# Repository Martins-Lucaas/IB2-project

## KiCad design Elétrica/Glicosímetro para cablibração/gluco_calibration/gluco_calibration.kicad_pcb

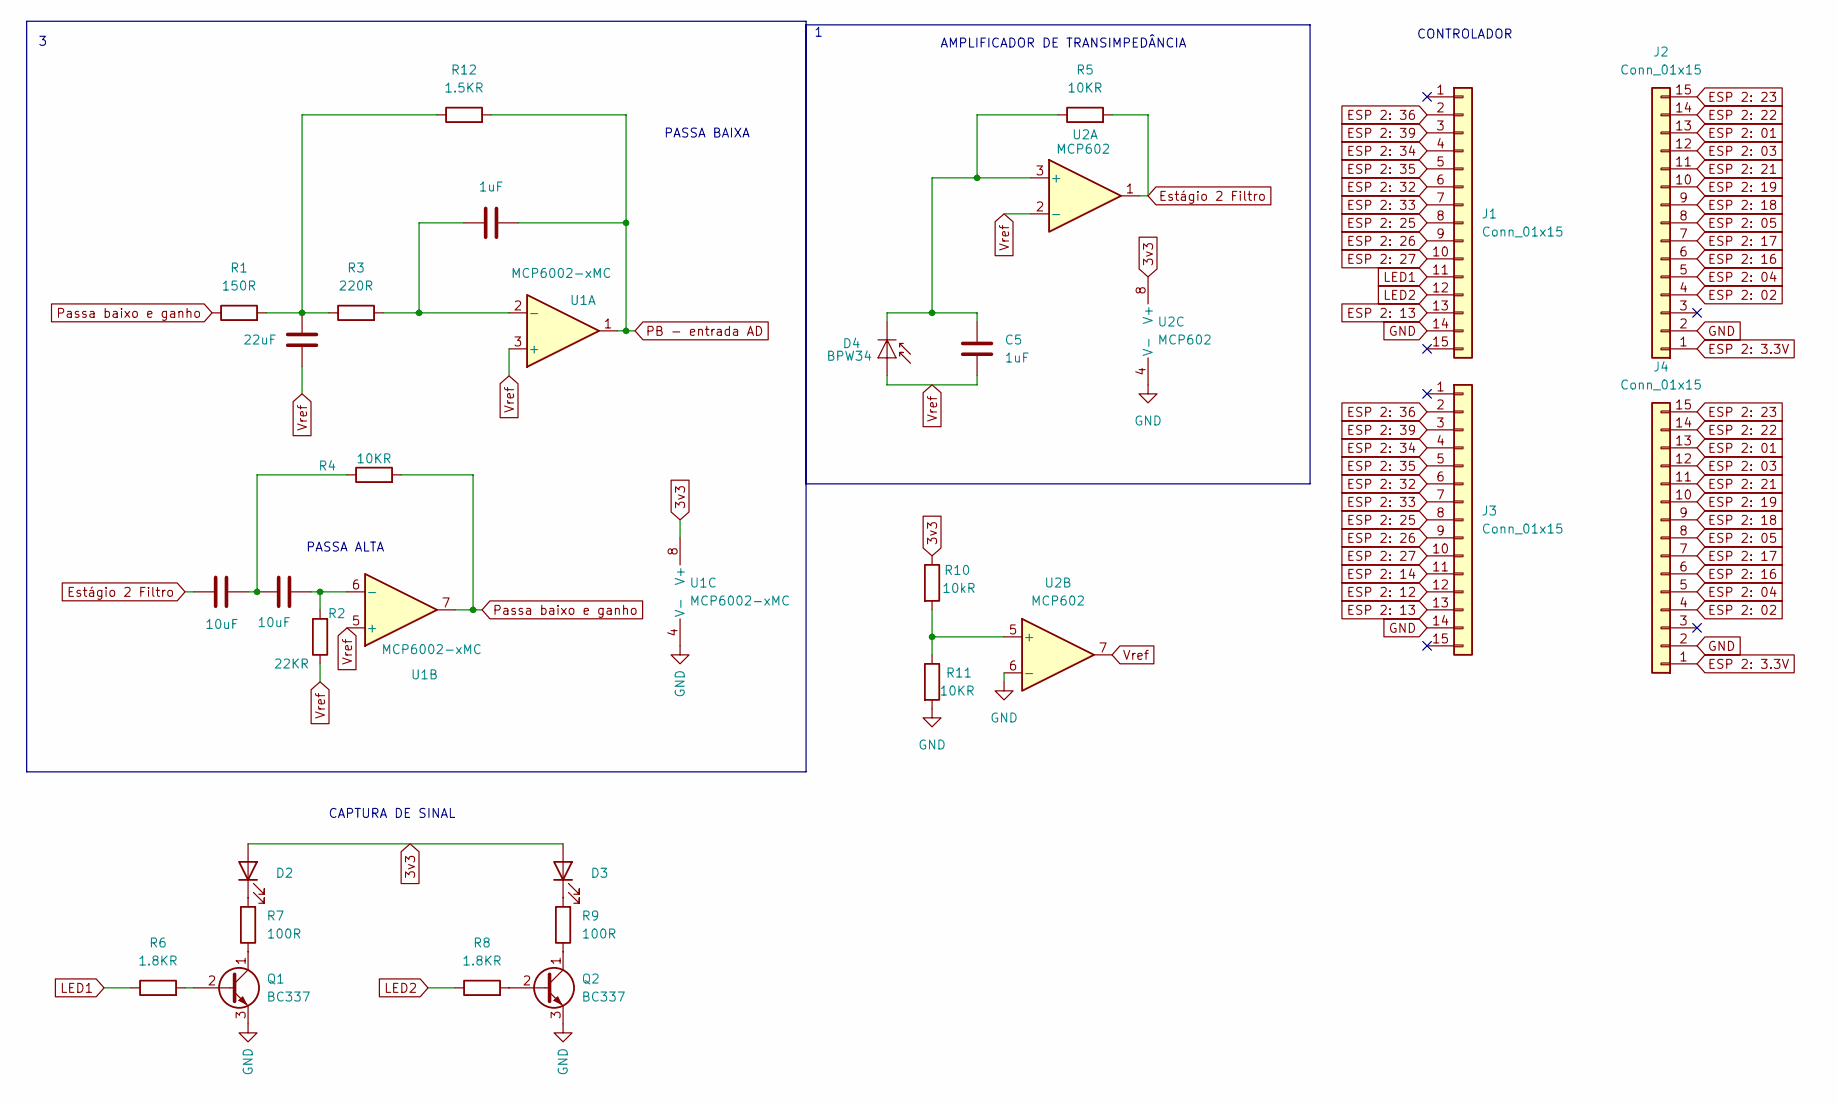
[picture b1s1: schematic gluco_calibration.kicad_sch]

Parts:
C1, C2: 10uF; C_Disc_D8.0mm_W2.5mm_P5.00mm
C3: 22uF; C_Disc_D8.0mm_W2.5mm_P5.00mm
C4, C5: 1uF; C_Disc_D8.0mm_W2.5mm_P5.00mm
D2: MTE8120CP 805nm; LED_D3.0mm_IRGrey
D3: MTE8120CP 805nm; LED_D3.0mm_Clear
D4: BPW34; Osram_DIL2_4.3x4.65mm_P5.08mm
J1, J2, J3, J4: Conn_01x15; PinSocket_1x15_P2.54mm_Vertical
Q1, Q2: BC337; TO-92_Inline
R1: 150R; R_Axial_DIN0204_L3.6mm_D1.6mm_P5.08mm_Horizontal
R2: 22KR; R_Axial_DIN0204_L3.6mm_D1.6mm_P5.08mm_Horizontal
R3: 220R; R_Axial_DIN0204_L3.6mm_D1.6mm_P5.08mm_Horizontal
R4, R5, R11: 10KR; R_Axial_DIN0204_L3.6mm_D1.6mm_P5.08mm_Horizontal
R6, R8: 1.8KR; R_Axial_DIN0204_L3.6mm_D1.6mm_P5.08mm_Horizontal
R7, R9: 100R; R_Axial_DIN0204_L3.6mm_D1.6mm_P5.08mm_Horizontal
R10: 10kR; R_Axial_DIN0204_L3.6mm_D1.6mm_P5.08mm_Horizontal
R12: 1.5KR; R_Axial_DIN0204_L3.6mm_D1.6mm_P5.08mm_Horizontal
U1: MCP6002-xMC; DFN-8-1EP_3x2mm_P0.5mm_EP1.75x1.45mm
U2: MCP602; DFN-8-1EP_3x2mm_P0.5mm_EP1.75x1.45mm

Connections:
3v3: D2.2 (A), D3.2 (A), R10.1, U1.8 (V+), U2.8 (V+)
ESP 2: 01: J2.13, J4.13
ESP 2: 02: J2.4, J4.4
ESP 2: 03: J2.12, J4.12
ESP 2: 3.3V: J2.1, J4.1
ESP 2: 04: J2.5, J4.5
ESP 2: 05: J2.8, J4.8
ESP 2: 12: J3.12
ESP 2: 13: J1.13, J3.13
ESP 2: 14: J3.11
ESP 2: 16: J2.6, J4.6
ESP 2: 17: J2.7, J4.7
ESP 2: 18: J2.9, J4.9
ESP 2: 19: J2.10, J4.10
ESP 2: 21: J2.11, J4.11
ESP 2: 22: J2.14, J4.14
ESP 2: 23: J2.15, J4.15
ESP 2: 25: J1.8, J3.8
ESP 2: 26: J1.9, J3.9
ESP 2: 27: J1.10, J3.10
ESP 2: 32: J1.6, J3.6
ESP 2: 33: J1.7, J3.7
ESP 2: 34: J1.4, J3.4
ESP 2: 35: J1.5, J3.5
ESP 2: 36: J1.2, J3.2
ESP 2: 39: J1.3, J3.3
Estágio 2 Filtro: C1.1, R5.2, U2.1
GND: J1.14, J2.2, J3.14, J4.2, Q1.3 (E), Q2.3 (E), R11.2, U1.4 (V-), U1.9 (V-), U2.4 (V-), U2.6 (-)
LED1: J1.11, R6.1
LED2: J1.12, R8.1
unnamed: C1.2, C2.1, R4.1
unnamed: C3.1, R1.2, R3.1, R12.1
unnamed: D2.1 (K), R7.2
unnamed: D3.1 (K), R9.2
unnamed: C5.1, D4.1 (K), R5.1, U2.3 (+)
unnamed: Q1.2 (B), R6.2
unnamed: Q1.1 (C), R7.1
unnamed: Q2.2 (B), R8.2
unnamed: Q2.1 (C), R9.1
unnamed: C4.1, R3.2, U1.2 (-)
unnamed: C2.2, R2.2, U1.6 (-)
unnamed: R10.2, R11.1, U2.5 (+)
PB - entrada AD: C4.2, R12.2, U1.1
Passa baixo e ganho: R1.1, R4.2, U1.7
Vref: C3.2, C5.2, D4.2 (A), R2.1, U1.3 (+), U1.5 (+), U2.2 (-), U2.7

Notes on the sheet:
CAPTURA DE SINAL
PASSA BAIXA
AMPLIFICADOR DE TRANSIMPEDÂNCIA
PASSA ALTA
CONTROLADOR

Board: 2 copper layers, 28 parts (0 on the bottom side), 43 nets, no tracks yet.

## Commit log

2024-05-29 Primeiro commit
2024-05-29 Trabalho 2 quase concluido
2024-05-30 Atualizações
2024-05-30 stop begin button working
2024-06-02 código e inicio da placa
2024-06-05 Atualizar o PotRead.ino
2024-06-05 mudou um parentis
    parentis
2024-06-10 Trabalho 1 completo
2024-06-10 inicio do app em flutter
2024-06-11 Trabalho 1 depois de cagarem regras
2024-06-11 Atualizações para a apresentação
2024-06-11 Revert "Atualizações para a apresentação"
    This reverts commit bf7e529a9c33260b3a6d9705da7ce7c06904d4f6.
2024-06-12 mudei foi tudo
    tome
2024-06-12 teste da aula
    testou
2024-06-18 Atualizar o Trabalho 2
2024-08-07 coisas
2024-08-07 Rename Osciloscopio_reg.ino to Oxímetro_reg.ino
2024-08-12 codigo
    mudei o nome do codigo
2024-08-12 mudei tudo
    td
2024-08-12 codigo teste
    low para high
2024-08-12 uns trem ai
    sei la
2024-08-12 mudei
    sei la
2024-08-13 placa de calibração
2024-08-13 tempo de pisca
    pisca
2024-08-13 mudei uns trem
    uns trem foi mudado
2024-08-13 nome
    tava o nome do daniel
2024-08-13 update
    update
2024-08-14 gambiarra do 1
    0 pra 1
2024-08-14 relatorio
    adicionei o pdf na pasta
2024-08-20 Adicionado aplicativo
2024-08-21 coloquei caixa de texto
    caixa de texto em partes do circuito
2024-08-21 fail
2024-08-21 transimpedancia
    mudei a entrada para a inversora
2024-08-26 portas
    portas output
2024-08-27 sei la
    se fode ai martins
2024-08-28 trab oxi
2024-09-09 codigo teste
    teste 09/09/2024
2024-09-10 trab4
2024-09-11 Trabalho4
2024-09-11 Trabalho 4
    aplicativo buildado
2024-09-13 trab para apresentação
2024-09-17 teste07-08
2024-09-17 atulizado 07-08
2024-09-17 sei la
    sei la
2024-09-17 função batimento
    batimento
2024-09-18 trabalho aquisição de dados
2024-09-18 codigo aquisição
    mudei taxa de aquisição fixa
2024-09-24 entrega oxi e dados
2024-09-25 datasheet
    coloquei o datasheet completo do esp32
2024-09-26 trabalhos entregues
2024-10-02 código de aula
    testes realizados em aula
2024-10-14 codigo frequencimetro
    atualizado
2024-10-15 aula 15/10/2024
    mudanças e codigo novo
2024-10-16 codigo final
    frequencimetro da balança final
2024-10-21 organização
2024-10-24 Arrumar arquivos
2024-10-25 Inicio MAPA
2024-10-28 controle valvula e bomba + comentarios + filtros
2024-10-28 atualização flutter
2024-10-29 sem app
2024-11-07 Versão final do código
2024-11-07 desespero
    desespero pra entregar o projeto
